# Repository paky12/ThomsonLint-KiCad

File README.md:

# ThomsonLint-KiCad

AI-powered hardware design review for KiCad projects. Fork of [ThomsonLint](https://github.com/holla2040/ThomsonLint) with native KiCad support.

Analyzes your schematics and PCB layouts against 158 engineering rules covering power integrity, high-speed routing, EMC, analog design, DFM, and more — then produces actionable findings with severity ratings.

## Quick Start

### 1. Install

```bash
git clone git@github.com:paky12/ThomsonLint-KiCad.git
cd ThomsonLint-KiCad
bash install.sh
```

The installer handles everything: Python dependencies, `kicad-cli` setup (including Flatpak), and Claude Code MCP server configuration.

Requires [uv](https://docs.astral.sh/uv/), **Python 3.10+**, and **KiCad 8+**.

<details>
<summary>Manual setup (if you prefer not to use the installer)</summary>

```bash
uv sync
```

**Flatpak users:** If you installed KiCad via Flatpak, `kicad-cli` won't be on your PATH. Create a wrapper script:
```bash
sudo tee /usr/local/bin/kicad-cli << 'EOF'
#!/bin/sh
exec flatpak run --command=kicad-cli org.kicad.KiCad "$@"
EOF
sudo chmod +x /usr/local/bin/kicad-cli
```

**Claude Code MCP server:** Add to `~/.claude/settings.json`:
```json
{
  "mcpServers": {
    "thomsonlint": {
      "command": "uv",
      "args": ["--directory", "/path/to/ThomsonLint-KiCad", "run", "thomsonlint", "serve"]
    }
  }
}
```

</details>

### 2. Use with Claude Code (recommended)

Then open Claude Code and ask:

> **"Review my KiCad design at ~/projects/my-board/my-board.kicad_pro"**

Claude will:
1. Export your schematic and PCB data (components, nets, traces, placement)
2. Load the 158-rule engineering knowledge base
3. Walk through each rule and report findings with severity ratings
4. Generate an interactive HTML report

That's it. No manual exporting, no prompt engineering.

### 3. Use from the command line

```bash
# Export KiCad project to ThomsonLint JSON
uv run thomsonlint export ~/projects/my-board/my-board.kicad_pro --output ./exports/

# Generate HTML report from review findings
uv run thomsonlint report findings.json --output ./exports/
```

The exported JSONs can be fed to any LLM along with `review_instructions.txt` for a manual review.

## What It Checks

| Domain | Examples | Rules |
|--------|---------|-------|
| **Power** | Missing decoupling, regulator placement, SMPS hot loops | 18 |
| **High-Speed** | Impedance control, diff pair routing, DDR length matching | 26 |
| **Analog** | Op-amp stability, ADC drivers, sensor front-ends | 11 |
| **EMC/ESD** | Missing TVS diodes, ground stitching, loop area | 12 |
| **DFM** | Acid traps, fiducials, BOM completeness | 24 |
| **DFT** | Test points, debug access, silkscreen labeling | 17 |
| **Thermal** | Power density, thermal vias, heat dissipation | 12 |
| **Component** | Voltage ratings, capacitor types, inductor saturation | 14 |
| **Schematic** | Floating inputs, single-pin nets, value errors | 14 |
| **Mechanical** | Connector stress, mounting holes, edge clearance | 6 |

## How It Works

```
KiCad Project (.kicad_pro)
    |
    |-- kicad-cli --> netlist, BOM, positions, drill data
    |-- .kicad_sch --> component pins, hierarchical sheets
    |-- .kicad_pcb --> traces, vias, zones, board outline
    |
    v
 Analyzers (signal classification, floating inputs,
            decoupling proximity, edge distances, ...)
    |
    v
 ThomsonLint JSON (same format as upstream)
    |
    v
 Claude Code + 158-rule knowledge base --> findings.json
    |
    v
 Interactive HTML report
```

**Dual-source data extraction:** `kicad-cli` provides structured exports (netlist XML, BOM, positions). Direct `.kicad_sch`/`.kicad_pcb` parsing provides data CLI can't export (trace lengths, via counts per net, zone pours, pad coordinates, board outline, layer stackup).

## MCP Tools

When running as an MCP server (`thomsonlint serve`), three tools are available:

| Tool | What it does |
|------|-------------|
| `export_kicad_project` | Parse KiCad project, run analysis, return schematic + board JSONs |
| `get_review_context` | Return the engineering knowledge base (ontology + rules + examples) |
| `generate_report` | Generate interactive HTML report from review findings |

## Requirements

- [**uv**](https://docs.astral.sh/uv/) — Python package manager
- **Python 3.10+**
- **KiCad 8+** with `kicad-cli` on PATH (see Flatpak note above if installed via Flatpak)
- **Claude Code** (for the MCP integration)

Python dependencies (managed by uv):
- `mcp` — Anthropic MCP SDK
- `jsonschema` — JSON validation

## Development

```bash
# Install with dev dependencies
uv sync --dev

# Run tests
uv run pytest tests/ -v

# Run tests with coverage
uv run pytest --cov=kicad --cov-report=html tests/
```

## Credits

Based on [ThomsonLint](https://github.com/holla2040/ThomsonLint) by holla2040. The ontology, knowledge base, examples, and report generator are from the upstream project. This fork adds KiCad export capability and MCP server integration.

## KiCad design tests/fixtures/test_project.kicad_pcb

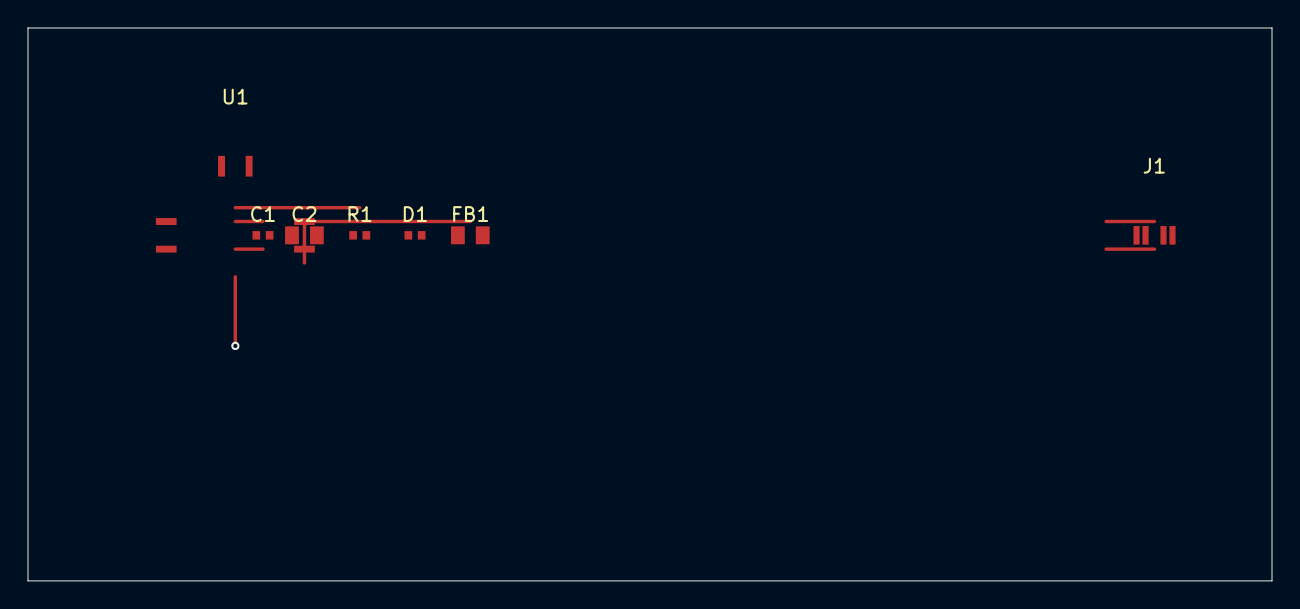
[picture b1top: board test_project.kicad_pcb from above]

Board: 2 copper layers, 90.0 x 40.0 mm, 7 parts (0 on the bottom side), 2 nets.

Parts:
C1: 100nF; C_0402_1005Metric
C2: 10uF; C_0805_2012Metric
D1: Green LED 0402; LED_0402_1005Metric
FB1: BLM21PG221SN1; L_0805_2012Metric
J1: USB_B_Micro; USB_Micro-B_Amphenol_10118194
R1: 10k; R_0402_1005Metric
U1: STM32F407VGTx; LQFP-100_14x14mm_P0.5mm

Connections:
GND: C1.2, C2.2, D1.K, FB1.2, J1.GND, U1.GND
VCC: C1.1, C2.1, D1.A, FB1.1, J1.VBUS, R1.1, U1.VCC

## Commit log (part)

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2026-03-19 feat: schematic analyzer — floating inputs, diff pairs, net classification
2026-03-19 feat: board analyzer — trace stats, decoupling proximity, edge distances
2026-03-19 feat: schematic exporter with JSON schema validation
2026-03-19 feat: board exporter with JSON schema validation
2026-03-19 feat: kicad-cli wrapper for netlist, BOM, positions, drill, DRC exports
2026-03-19 feat: CLI entry point — export, serve, report subcommands
2026-03-19 feat: MCP server with export, review context, and report tools
2026-03-19 fix: correct netlist parser import name in CLI
2026-03-19 docs: update README for KiCad fork with install, MCP, and CLI instructions
2026-03-19 docs: use uv instead of pip in README
2026-03-19 docs: add CLAUDE.md and update CONTRIBUTING.md for KiCad fork
2026-03-19 docs: add real-design testing guide and benchmark checklist
